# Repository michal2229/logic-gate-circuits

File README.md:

## logic-gate-circuits

My old university projects in logic gate circuits synthesis made in MICROWIND DSCH 3.5 software.

I made them during my studies at Military University of Technology, Warsaw, Poland.

Some of them I wrote for myself but vast majority of them I wrote to teach others.

Repository tree:

```
.
├── README.md
├── 1224
│   ├── blok.sym
│   ├── sch_2wys.sch
│   ├── schemat2.sch
│   ├── schemat2.txt
│   └── uklad_obrazek.png
├── 1z10
│   ├── obrazki
│   │   ├── 14B_ADD.png
│   │   ├── 1z10_hex.png
│   │   ├── dec_hex_schemat polaczen.png
│   │   ├── katalogowy.png
│   │   ├── mul10.png
│   │   ├── sumator.png
│   │   └── uklad_caly.png
│   ├── parts
│   │   ├── 16B_ADD.sch
│   │   ├── 16B_ADD.sym
│   │   ├── 1z10_hex.sch
│   │   ├── 1z10_hex.sym
│   │   ├── mul10.sch
│   │   ├── mul10.sym
│   │   ├── sumator.sch
│   │   └── sumator.sym
│   ├── sch_ost_dziala2.sch
│   └── ti_sn54f283.pdf
├── 1z16_7seg
│   ├── 0tof.png
│   ├── 1z16_7seg_2.sch
│   ├── 1z16_7seg-eagle.sch
│   ├── 1z16_7seg.sch
│   ├── digit6.png
│   ├── elkat.png
│   └── schemat.png
├── 1z8
│   ├── 1z8_hex.sch
│   ├── 1z8_hex.sym
│   ├── 1z8_hex.v
│   ├── obrazki
│   │   ├── 14B_ADD.png
│   │   ├── 1z10_hex.png
│   │   ├── dec_hex_schemat polaczen.png
│   │   ├── katalogowy.png
│   │   ├── mul10.png
│   │   ├── sumator.png
│   │   └── uklad_caly.png
│   ├── parts
│   │   ├── 16B_ADD.sch
│   │   ├── 16B_ADD.sym
│   │   ├── 1z10_hex.sch
│   │   ├── 1z10_hex.sym
│   │   ├── 1z8_hex.sch
│   │   ├── 1z8_hex.sym
│   │   ├── 1z8_hex.v
│   │   ├── mul10.sch
│   │   ├── mul10.sym
│   │   ├── sumator.sch
│   │   └── sumator.sym
│   ├── sch_ost_dziala3.sch
│   └── ti_sn54f283.pdf
├── 1z8 na dec
│   ├── obrazki
│   │   ├── 14B_ADD.png
│   │   ├── 1z10_hex.png
│   │   ├── dec_hex_schemat polaczen.png
│   │   ├── katalogowy.png
│   │   ├── mul10.png
│   │   ├── sumator.png
│   │   └── uklad_caly.png
│   ├── parts
│   │   ├── 16B_ADD.sch
│   │   ├── 16B_ADD.sym
│   │   ├── 1z10_hex.sch
│   │   ├── 1z10_hex.sym
│   │   ├── mul10.sch
│   │   ├── mul10.sym
│   │   ├── sumator.sch
│   │   └── sumator.sym
│   ├── sch_ost_dziala2.sch
│   └── ti_sn54f283.pdf
├── div43
│   └── div43.sch
├── div59
│   ├── czas.png
│   ├── div37.sch
│   ├── div59_eagle.sch
│   ├── div59.sch
│   ├── katalogowy.png
│   ├── schemat.png
│   ├── Zrzut ekranu 2013-11-17 00.12.30.png
│   └── Zrzut ekranu 2013-11-17 00.12.52.png
├── div71
│   ├── div71-eagle.sch
│   ├── div71_.sch
│   ├── div71.sch
│   └── div71-uklad-katalogowy.png
├── dod_hex
│   ├── elkat.png
│   ├── inv4.sym
│   ├── inv.sym
│   ├── inv.v
│   ├── schemat.png
│   └── sum_hex.sch
├── dod_u2
│   ├── inv4.sym
│   ├── inv4+.sym
│   ├── inv_GND.sch
│   ├── inv_GND.v
│   ├── inv.png
│   ├── inv_.sch
│   ├── inv.sch
│   ├── inv.sym
│   ├── inv.v
│   ├── inwerter.png
│   ├── program_do_8051.asm
│   ├── schemat-eagle.png
│   ├── schemat_eagle.sch
│   ├── schemat_.png
│   ├── schemat.png
│   ├── schemat.sch
│   ├── sum1.png
│   ├── sum1.sch
│   ├── sum1.sym
│   ├── sum1.v
│   ├── sum_4b+.sch
│   ├── sum_4b+.sym
│   ├── sum_4b+.v
│   ├── sum4.png
│   ├── sum4.sch
│   ├── sum4.sym
│   ├── sum4.v
│   ├── sumator.png
│   ├── symbole.png
│   ├── uklad-eagle.png
│   ├── ukl-eagle.sch
│   └── ukl.sch
├── hex to bcd
│   └── hex2bcd.sch
├── klaw_bcd
│   ├── eagle
│   │   ├── klaw2bcd.brd
│   │   ├── klaw2bcd.pdf
│   │   ├── klaw2bcd.pro
│   │   └── klaw2bcd.sch
│   ├── klaw2bcd-dsch35.png
│   ├── klaw2bcd.png
│   ├── KLAW2BCD.sch
│   ├── opis.txt
│   └── sn74ls147 - Encode 10-Line Decimal to 4-Line BCD.pdf
├── komparator
│   └── komp2.sch
├── mier_pr_obr
│   ├── licz8b_D.sch
│   ├── licz8b_D.sym
│   ├── licz8b_D.v
│   ├── MC74HC4024N.pdf
│   ├── mie_pr_o_eagle.brd
│   ├── mie_pr_o_eagle.sch
│   ├── mie_pr_o.sch
│   └── schemat eagle.png
├── mod11
│   ├── 220px-Intel_8253_and_8254.svg.png
│   ├── el_kat.png
│   ├── m11_not.sch
│   ├── mod11_czas.png
│   ├── mod11.png
│   └── mul22.png
├── mod13
│   └── liczn_mod_13.sch
├── mod7mul
│   ├── 7_.png
│   ├── mod7_rs.sch
│   └── mod7___.sch
├── nieparzystosc
│   ├── parzystosc.sch
│   ├── uklad-eagle.sch
│   └── uklad-katalogowy-parzystosc.png
├── parzystosc
│   ├── parzystosc.sch
│   └── uklad-katalogowy-parzystosc.png
├── pierw_3
│   ├── bramki wysylajace impulsy przy przechodzeniu przez odpowiednia liczbe.png
│   ├── klawiatura i uklad konczacy liczenie.png
│   ├── liczby i ich pierwiastki.txt
│   ├── licznik2.png
│   ├── pierw_3.ods
│   ├── pierw.sch
│   ├── schemat-eagle.sch
│   ├── uklad-eagle.png
│   └── uklad.png
├── por_licz
│   ├── dectobin.png
│   ├── dec_to_bin.sch
│   ├── dec_to_bin.sym
│   ├── dec_to_bin.v
│   ├── POR_LICZ-eagle.sch
│   ├── POR_LICZ.sch
│   ├── schemat_dsch3.png
│   ├── schemat_kat.png
│   ├── sub1b.png
│   ├── sub1b.sch
│   ├── sub1b.sym
│   ├── sub1b.v
│   ├── sub4b.png
│   ├── sub4b.sch
│   ├── sub4b.sym
│   └── sub4b.v
├── porownywator
│   ├── schemat dsch3.png
│   └── schemat dsch3 katalogowe.png
├── prost
│   └── prost.sch
├── rej szer dwuk 4b - dsch3
│   ├── 1bitrej.sch
│   ├── 1bitrej.sym
│   ├── 1bitrej.v
│   ├── 1bshr.sym
│   ├── cd74hc165.pdf
│   ├── KL_Intel_P8051.jpg
│   ├── rejdwuk_sz.sch
│   ├── sn74als164a.pdf
│   ├── Zrzut ekranu 2013-11-01 03.53.04.png
│   └── Zrzut ekranu 2013-11-01 03.54.26.png
├── serce
│   ├── example
│   ├── inv4+.sym
│   ├── inv8b.sym
│   ├── inv.sch
│   ├── inv.v
│   ├── licz_8b.sch
│   ├── licz_8b.sym
│   ├── licz_8b.v
│   ├── sub1b.sch
│   ├── sub1b.sym
│   ├── sub1b.v
│   ├── sub4b.sch
│   ├── sub4b.sym
│   ├── sub4b.v
│   ├── sub8b.sch
│   ├── sub8b.sym
│   ├── sub8b.v
│   ├── sum_4b+.sch
│   ├── sum_4b+.sym
│   ├── sum_4b+.v
│   ├── uklad.png
│   ├── ukl-eagle.brd
│   ├── ukl-eagle.pro
│   ├── ukl-eagle.sch
│   ├── ukl.sch
│   ├── ukl.v
│   └── Zrzut ekranu 2013-11-22 01.19.46.png
├── submul
│   ├── mul4b.sch
│   ├── mul4b.sym
│   ├── mul4b.txt
│   ├── sub4b.sch
│   ├── sub4b.txt
│   ├── sub_A_B.sym
│   ├── subfull.sch
│   ├── subfull.sym
│   ├── subfull.txt
│   └── uklad.sch
├── subtraktor i multiplikator
│   ├── 1badder.png
│   ├── 1badder.sch
│   ├── 1badder.sym
│   ├── 1badder.v
│   ├── 1bsub.png
│   ├── 1bsub.sch
│   ├── 1bsub.sym
│   ├── 1bsub.v
│   ├── 4bsub.png
│   ├── 4bsub.sch
│   ├── 8badder.png
│   ├── 8badder.sch
│   ├── 8badder.sym
│   ├── 8badder.v
│   ├── 8bsub.sym
│   ├── 8bsub.v
│   ├── kod_programu_na_8051.asm
│   ├── MULTIPLIKATOR.sch
│   ├── schemat-dsch3.png
│   ├── schemat-eagle.png
│   └── schemat-eagle.sch
├── sumul
│   ├── aassd.SCH
│   ├── ideowy z katalogowymi.png
│   ├── mul_4b.sch
│   ├── schemat dsch3 mul.png
│   ├── schemat dsch3 sum.png
│   ├── schemat dsch3 sumul.png
│   ├── sumabppw.sch
│   └── sumul_hex.sch
├── sum z mul
│   ├── mul_4b.sch
│   ├── sumabppw.sch
│   └── sumul_hex.sch
├── sygnalizacja
│   ├── schemat.png
│   ├── swiatla.sch
│   └── time_diag.png
├── ucm lab przerzutniki chwytak robot
│   ├── 1_d_ff.sch
│   ├── 2_d_syn.sch
│   ├── 3_d_syn-.sch
│   ├── chwytak_rs.s
│   ├── chwyt_rs.sch
│   ├── example
│   ├── robott.sch
│   ├── RS_blok.sym
│   ├── RS-sch.sch
│   ├── RS-sch.txt
│   └── rs_v2.sch
└── ukl inc o 1 - dsch3
    ├── inc1_osc.sch
    ├── inc1.sch
    └── licznik.png
```

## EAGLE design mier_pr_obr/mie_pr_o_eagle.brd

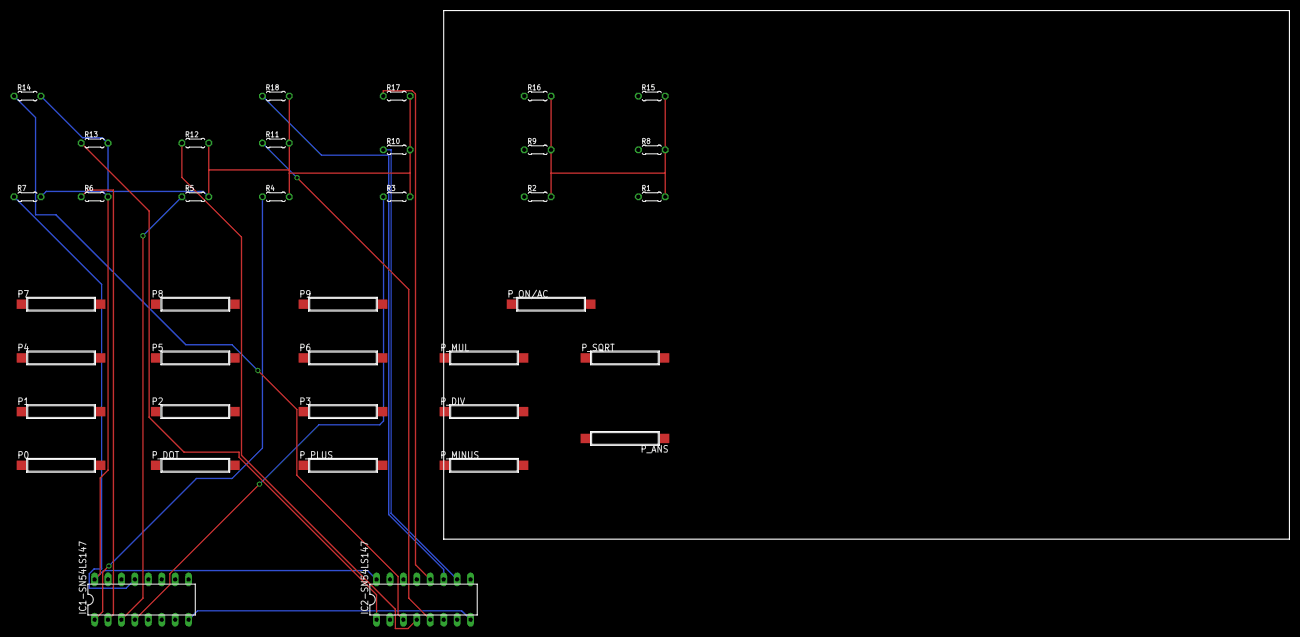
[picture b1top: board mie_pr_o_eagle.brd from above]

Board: 2 copper layers, 238.9 x 100.0 mm, 38 parts (0 on the bottom side), 20 nets.

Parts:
IC1-SN54LS147, IC2-SN54LS147: 74HC147N; DIL16
P0, P1, P2, P3, P4, P5, P6, P7, P8, P9: CT10-XXXX-A2
P_ANS: CT10-XXXX-A2
P_DIV: CT10-XXXX-A2
P_DOT: CT10-XXXX-A2
P_MINUS: CT10-XXXX-A2
P_MUL: CT10-XXXX-A2
P_ON/AC: CT10-XXXX-A2
P_PLUS: CT10-XXXX-A2
P_SQRT: CT10-XXXX-A2
R1, R2, R3, R4, R5, R6, R7, R8, R9, R10, R11, R12, R13, R14, R15, R16, R17, R18: 0204/5

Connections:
GND: IC1-SN54LS147.8, IC2-SN54LS147.8, P0.1, P1.1, P2.1, P3.1, P4.1, P5.1, P6.1, P7.1, P8.1, P9.1, P_ANS.1, P_DIV.1, P_DOT.1, P_MINUS.1, P_MUL.1, P_ON/AC.1, P_PLUS.1, P_SQRT.1
unnamed: IC1-SN54LS147.11, P1.2, R9.1
unnamed: IC1-SN54LS147.12, P2.2, R8.1
unnamed: IC1-SN54LS147.13, P3.2, R7.1
unnamed: IC1-SN54LS147.1, P4.2, R4.1
unnamed: IC1-SN54LS147.2, P5.2, R6.1
unnamed: IC1-SN54LS147.3, P6.2, R5.1
unnamed: IC1-SN54LS147.4, P7.2, R3.1
unnamed: IC1-SN54LS147.5, P8.2, R2.1
unnamed: IC1-SN54LS147.10, P9.2, R1.1
unnamed: IC2-SN54LS147.11, P0.2, R18.1
unnamed: IC2-SN54LS147.12, P_SQRT.2, R17.1
unnamed: IC2-SN54LS147.13, P_MUL.2, R16.1
unnamed: IC2-SN54LS147.1, P_DIV.2, R13.1
unnamed: IC2-SN54LS147.2, P_ON/AC.2, R15.1
unnamed: IC2-SN54LS147.3, P_DOT.2, R14.1
unnamed: IC2-SN54LS147.4, P_ANS.2, R12.1
unnamed: IC2-SN54LS147.5, P_MINUS.2, R11.1
unnamed: IC2-SN54LS147.10, P_PLUS.2, R10.1
VCC: IC1-SN54LS147.16, IC2-SN54LS147.16, R1.2, R2.2, R3.2, R4.2, R5.2, R6.2, R7.2, R8.2, R9.2, R10.2, R11.2, R12.2, R13.2, R14.2, R15.2, R16.2, R17.2, R18.2

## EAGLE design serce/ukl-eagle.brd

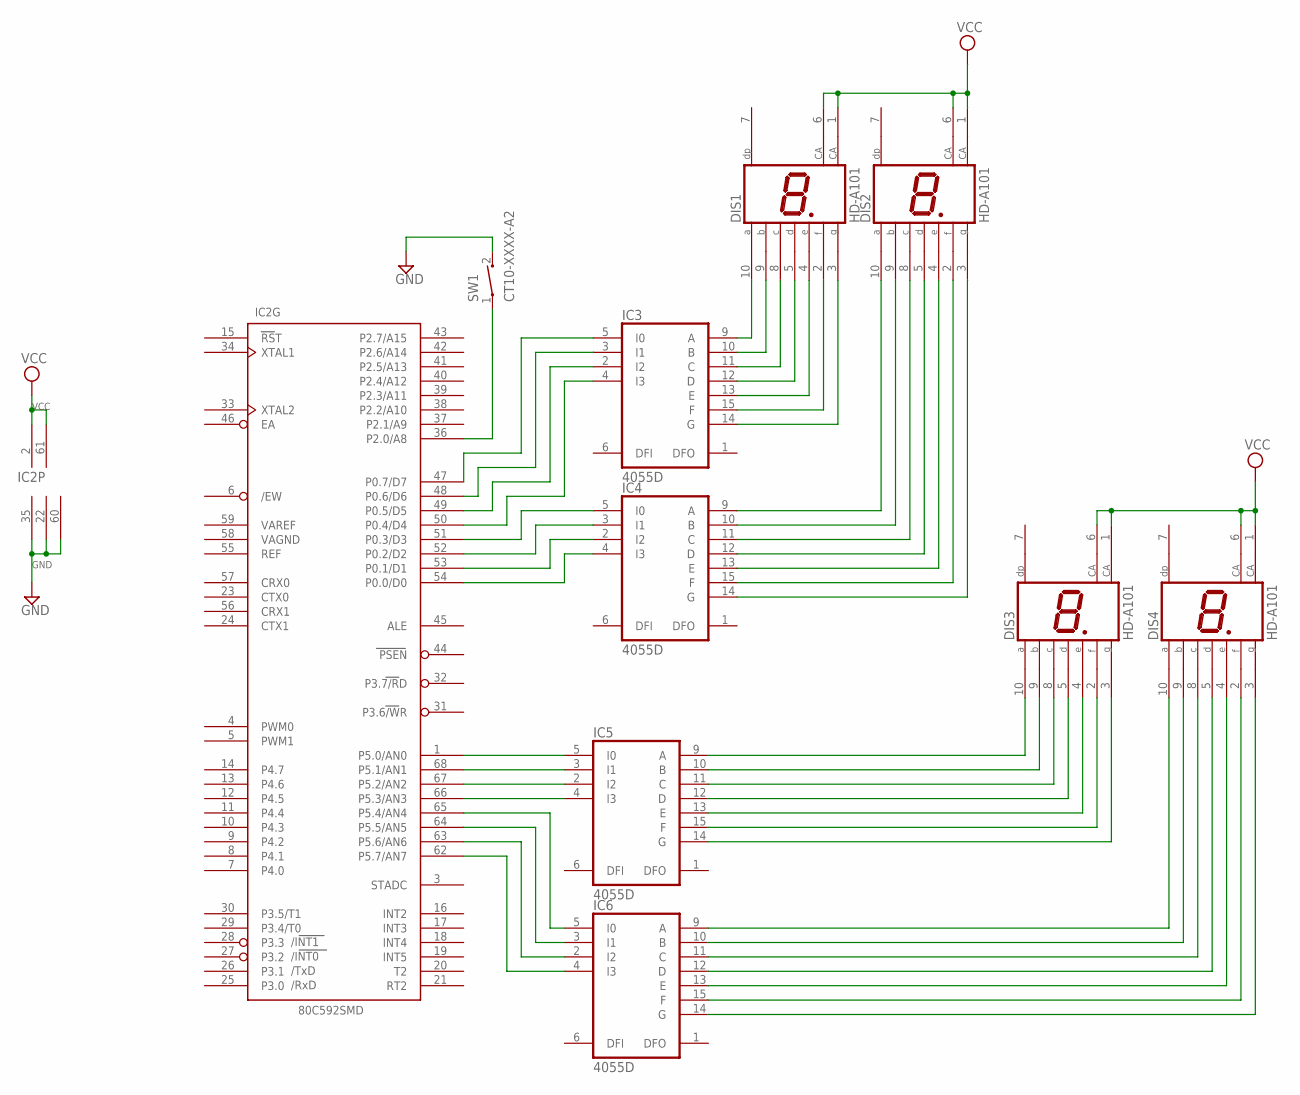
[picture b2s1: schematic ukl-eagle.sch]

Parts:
DIS1, DIS2, DIS3, DIS4: HD-A101; HDSP-A
IC2: 80C592SMD; PLCC68
IC3, IC4, IC5, IC6: 4055D; SO16
SW1: CT10-XXXX-A2

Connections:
GND: IC2.22 (CGND), IC2.35 (GND), IC2.60 (AGND), IC3.8 (GND), IC4.8 (GND), IC5.8 (GND), IC6.8 (GND), SW1.2
unnamed: DIS1.10 (A), IC3.9 (A)
unnamed: DIS1.9 (B), IC3.10 (B)
unnamed: DIS1.8 (C), IC3.11 (C)
unnamed: DIS1.5 (D), IC3.12 (D)
unnamed: DIS1.4 (E), IC3.13 (E)
unnamed: DIS1.2 (F), IC3.15 (F)
unnamed: DIS1.3 (G), IC3.14 (G)
unnamed: DIS2.10 (A), IC4.9 (A)
unnamed: DIS2.9 (B), IC4.10 (B)
unnamed: DIS2.3 (G), IC4.14 (G)
unnamed: DIS2.2 (F), IC4.15 (F)
unnamed: DIS2.4 (E), IC4.13 (E)
unnamed: DIS2.5 (D), IC4.12 (D)
unnamed: DIS2.8 (C), IC4.11 (C)
unnamed: DIS3.10 (A), IC5.9 (A)
unnamed: DIS3.9 (B), IC5.10 (B)
unnamed: DIS3.8 (C), IC5.11 (C)
unnamed: DIS3.5 (D), IC5.12 (D)
unnamed: DIS3.4 (E), IC5.13 (E)
unnamed: DIS3.2 (F), IC5.15 (F)
unnamed: DIS3.3 (G), IC5.14 (G)
unnamed: DIS4.10 (A), IC6.9 (A)
unnamed: DIS4.9 (B), IC6.10 (B)
unnamed: DIS4.8 (C), IC6.11 (C)
unnamed: DIS4.5 (D), IC6.12 (D)
unnamed: DIS4.4 (E), IC6.13 (E)
unnamed: DIS4.2 (F), IC6.15 (F)
unnamed: DIS4.3 (G), IC6.14 (G)
unnamed: IC2.54 (P0.0/D0), IC4.4 (I3)
unnamed: IC2.53 (P0.1/D1), IC4.2 (I2)
unnamed: IC2.52 (P0.2/D2), IC4.3 (I1)
unnamed: IC2.51 (P0.3/D3), IC4.5 (I0)
unnamed: IC2.50 (P0.4/D4), IC3.4 (I3)
unnamed: IC2.49 (P0.5/D5), IC3.2 (I2)
unnamed: IC2.48 (P0.6/D6), IC3.3 (I1)
unnamed: IC2.47 (P0.7/D7), IC3.5 (I0)
unnamed: IC2.36 (P2.0/A8), SW1.1
unnamed: IC2.1 (P5.0/AN0), IC5.5 (I0)
unnamed: IC2.68 (P5.1/AN1), IC5.3 (I1)
unnamed: IC2.67 (P5.2/AN2), IC5.2 (I2)
unnamed: IC2.66 (P5.3/AN3), IC5.4 (I3)
unnamed: IC2.65 (P5.4/AN4), IC6.5 (I0)
unnamed: IC2.64 (P5.5/AN5), IC6.3 (I1)
unnamed: IC2.63 (P5.6/AN6), IC6.2 (I2)
unnamed: IC2.62 (P5.7/AN7), IC6.4 (I3)
VCC: DIS1.1 (CA), DIS3.1 (CA), DIS3.6 (CA), DIS4.1 (CA), DIS4.6 (CA), IC2.2 (VCC), IC2.61 (AVCC), IC3.16 (VCC), IC4.16 (VCC), IC5.16 (VCC), IC6.16 (VCC)
VEE: IC3.7 (VEE), IC4.7 (VEE), IC5.7 (VEE), IC6.7 (VEE)

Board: 2 copper layers, 10 parts (0 on the bottom side), 48 nets, no tracks yet.

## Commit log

2016-10-21 init
2016-10-21 readme
